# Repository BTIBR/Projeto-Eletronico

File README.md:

# Projeto-Eletronico

Projeto Eletrônico da PCI que contém o driver de controle dos motores de passo do Braço Robótico Leticya

### Software
- KiCad v5.1.9+

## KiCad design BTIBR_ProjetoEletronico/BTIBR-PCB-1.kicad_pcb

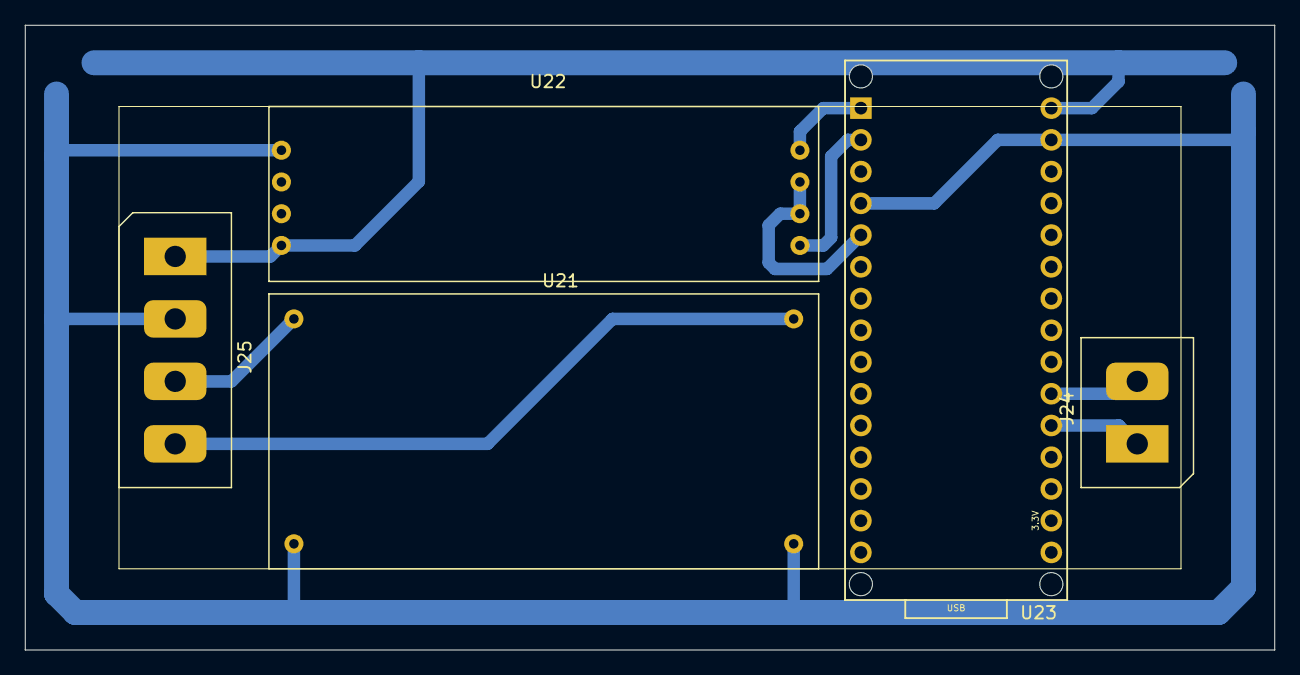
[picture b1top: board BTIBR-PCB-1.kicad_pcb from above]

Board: 2 copper layers, 100.0 x 50.0 mm, 5 parts (0 on the bottom side), 9 nets.

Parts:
J24: Screw_Terminal_01x02; Connector_Screw_2pin
J25: Screw_Terminal_01x04; Connector_Screw_4pin
U21: Module_LM2596
U22: Module_MAX485
U23: Arduino_Socket_Nano

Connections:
+5V: J25.1, U22.VCC, U23.VIN
+8V: J25.4, U21.OUT+
+12V: J25.3, U21.IN+
GND: J25.2, U21.IN-, U21.OUT-, U22.GND, U23.GND1, U23.GND2
unnamed: J24.1, U23.A1
unnamed: J24.2, U23.A2
unnamed: U22.DE, U22.RE, U23.D2
unnamed: U22.DI, U23.D1
unnamed: U22.RO, U23.D0

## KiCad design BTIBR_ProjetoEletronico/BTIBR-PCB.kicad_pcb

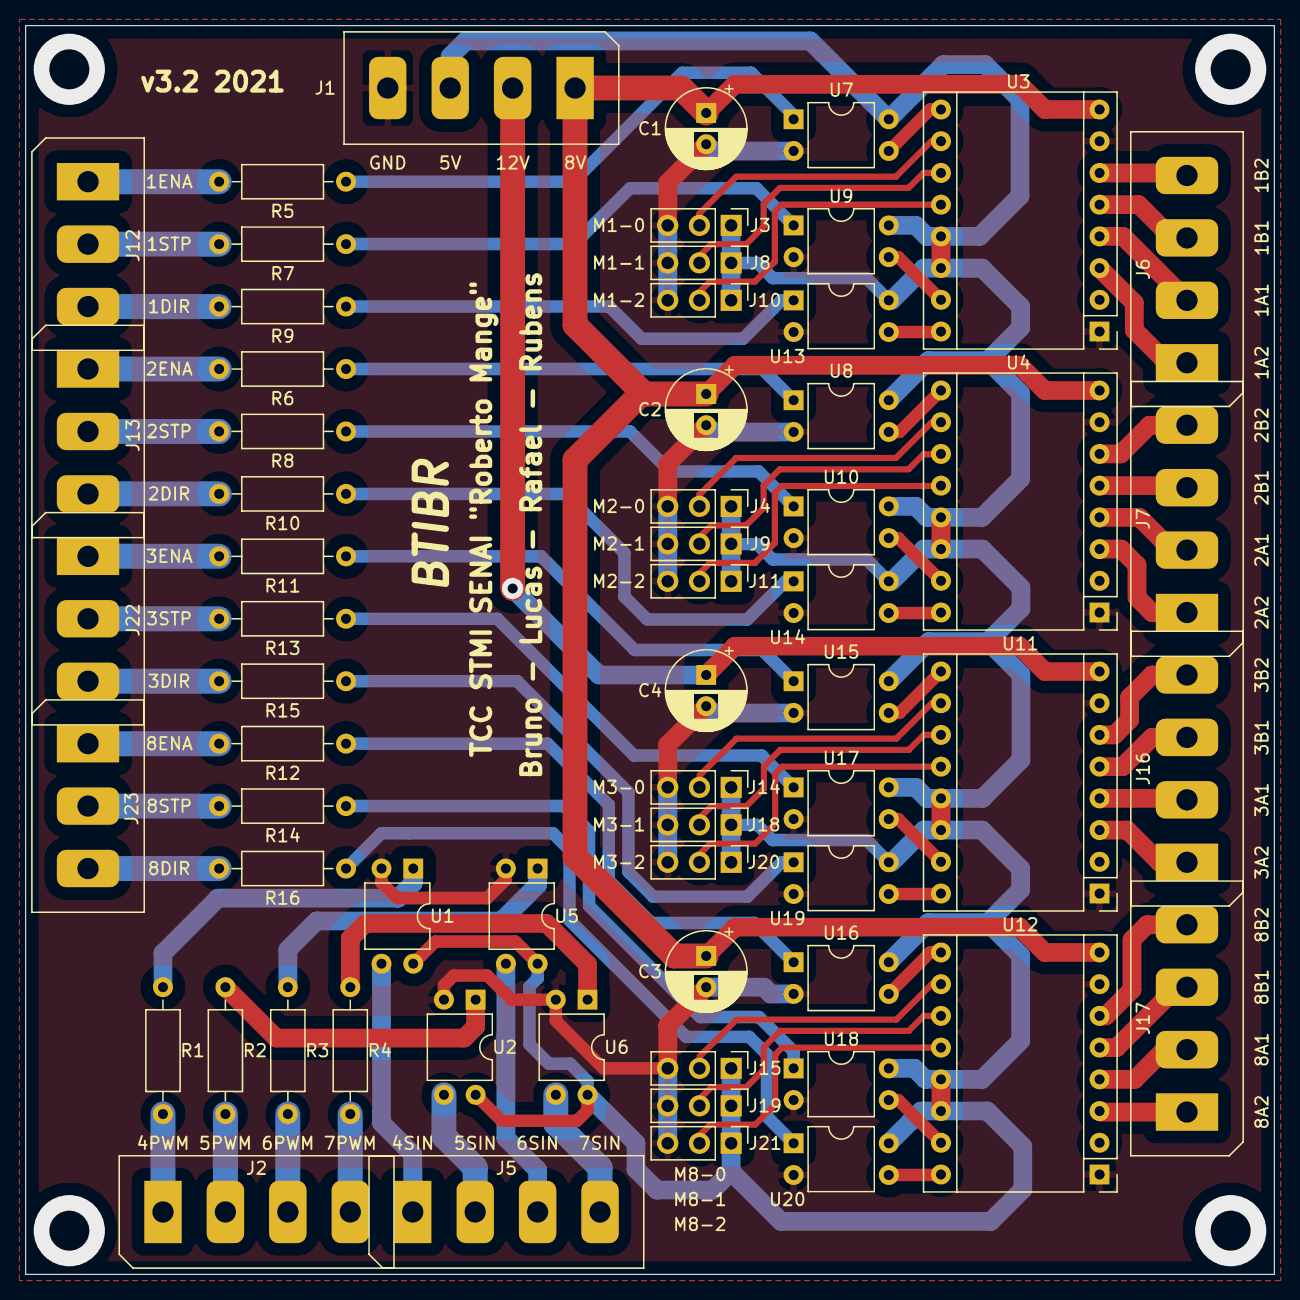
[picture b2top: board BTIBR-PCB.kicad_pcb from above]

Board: 2 copper layers, 100.0 x 100.0 mm, 63 parts (0 on the bottom side), 80 nets.

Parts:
C1, C2, C3, C4: 100 μF; CP_Radial_D6.3mm_P2.50mm
J1, J2, J5, J6, J7, J16, J17: Screw_Terminal_01x04; Connector_Screw_4pin
J3, J4, J8, J9, J10, J11, J14, J15, J18, J19, J20, J21: Conn_01x03_Male; PinHeader_1x03_P2.54mm_Vertical
J12, J13, J22, J23: Screw_Terminal_01x03; Connector_Screw_3pin
R1, R2, R3, R4, R5, R6, R7, R8, R9, R10, R11, R12, R13, R14, R15, R16: 1k; R_Axial_DIN0207_L6.3mm_D2.5mm_P10.16mm_Horizontal
U1, U2, U5, U6, U7, U8, U9, U10, U13, U14, U15, U16, U17, U18, U19, U20: PC817; DIP-4_W7.62mm
U3, U4, U11, U12: DRV8825; Module_DRV8825

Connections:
+5V: J1.3, J3.1, J4.1, J8.1, J9.1, J10.1, J11.1, J14.1, J15.1, J18.1, J19.1, J20.1, J21.1, U1.4, U2.4, U3.13, U3.14, U4.13, U4.14, U5.4, U6.4, U7.4, U8.4, U9.4, U10.4, U11.13, U11.14, U12.13, U12.14, U13.4, U14.4, U15.4, U16.4, U17.4, U18.4, U19.4, U20.4
+8V: C1.1, C2.1, C3.1, J1.1, U3.8, U4.8, U12.8
+12V: C4.1, J1.2, U11.8
GND: C1.2, C2.2, C3.2, C4.2, J1.4, J3.3, J4.3, J8.3, J9.3, J10.3, J11.3, J14.3, J15.3, J18.3, J19.3, J20.3, J21.3, U1.2, U2.2, U3.1, U3.7, U4.1, U4.7, U5.2, U6.2, U7.2, U8.2, U9.2, U10.2, U11.1, U11.7, U12.1, U12.7, U13.2, U14.2, U15.2, U16.2, U17.2, U18.2, U19.2, U20.2
M1_DIR: U3.16, U13.3
M1_EN: U3.9, U7.3
M1_M0: J3.2, U3.10
M1_M1: J8.2, U3.11
M1_M2: J10.2, U3.12
M1_STEP: U3.15, U9.3
M2_DIR: U4.16, U14.3
M2_EN: U4.9, U8.3
M2_M0: J4.2, U4.10
M2_M1: J9.2, U4.11
M2_M2: J11.2, U4.12
M2_STEP: U4.15, U10.3
M3_DIR: U11.16, U19.3
M3_EN: U11.9, U15.3
M3_M0: J14.2, U11.10
M3_M1: J18.2, U11.11
M3_M2: J20.2, U11.12
M3_STEP: U11.15, U17.3
M8_DIR: U12.16, U20.3
M8_EN: U12.9, U16.3
M8_M0: J15.2, U12.10
M8_M1: J19.2, U12.11
M8_M2: J21.2, U12.12
M8_STEP: U12.15, U18.3
unnamed: J2.1, R1.2
unnamed: J2.2, R2.2
unnamed: J2.3, R3.2
unnamed: J2.4, R4.2
unnamed: J5.1, U1.3
unnamed: J5.2, U2.3
unnamed: J5.3, U5.3
unnamed: J5.4, U6.3
unnamed: J6.1, U3.3
unnamed: J6.2, U3.4
unnamed: J6.3, U3.5
unnamed: J6.4, U3.6
unnamed: J7.1, U4.3
unnamed: J7.2, U4.4
unnamed: J7.3, U4.5
unnamed: J7.4, U4.6
unnamed: J12.1, R5.2
unnamed: J12.2, R7.2
unnamed: J12.3, R9.2
unnamed: J13.1, R6.2
unnamed: J13.2, R8.2
unnamed: J13.3, R10.2
unnamed: J16.1, U11.3
unnamed: J16.2, U11.4
unnamed: J16.3, U11.5
unnamed: J16.4, U11.6
unnamed: J17.1, U12.3
unnamed: J17.2, U12.4
unnamed: J17.3, U12.5
unnamed: J17.4, U12.6
unnamed: J22.1, R11.2
unnamed: J22.2, R13.2
unnamed: J22.3, R15.2
unnamed: J23.1, R12.2
unnamed: J23.2, R14.2
unnamed: J23.3, R16.2
unnamed: R1.1, U1.1
unnamed: R2.1, U2.1
unnamed: R3.1, U5.1
unnamed: R4.1, U6.1
unnamed: R5.1, U7.1
unnamed: R6.1, U8.1
unnamed: R7.1, U9.1
unnamed: R8.1, U10.1
unnamed: R9.1, U13.1
unnamed: R10.1, U14.1
unnamed: R11.1, U15.1
unnamed: R12.1, U16.1
unnamed: R13.1, U17.1
unnamed: R14.1, U18.1
unnamed: R15.1, U19.1
unnamed: R16.1, U20.1

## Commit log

2021-05-19 Add backup desenvolvimento 2019-2020
2021-05-20 Correção da estrutura de pastas
2021-05-20 Correção do footprint do modulo pot digital
2021-05-31 Adicionada BOM List customizada
2021-06-05 Correção na resistencia Rs
2021-06-12 Correção do tipo de gráfico nas simulações
2021-06-15 Adicionada planilha dos testes da placa
2021-06-19 Alterada a resistencia do RV1
2021-07-04 Correções mínimas
2021-07-30 Início da versão 3 do projeto eletrônico
2021-07-30 Adicionada página para CLP e segunda fonte
2021-07-30 Adicionados barramentos das alimentações
2021-07-31 Finalizada a versao 3.0 do esquemático
2021-07-31 Removido reglador de tensao da PCB
2021-07-31 Finalizado desenvolvimento da PCB
2021-08-01 Gerados arquivos de fabricação (Gerber)
2021-08-01 Atualizada BOM List da placa
2021-08-03 Adicionados arquivos antigos dos calculos da eletronica (Jupyter Notebook)
2021-09-10 Adicionado módulo da célula de carga
2021-09-22 Adicionados Datasheets dos Servos
2021-10-03 Adicionada célula de carga e arduino ao projeto, com comunicação RS485 com o CLP
2021-10-09 Adicionada PCB-1 (Arduino, LM2596 e MAX485)
2021-10-11 Finalizado layout da PCB-1
2021-10-11 Finalização da verão 3.2 do esquemático
2021-11-14 Adicionado poste luminoso
2021-12-02 Adicionado cor dos cabos celula de carga
